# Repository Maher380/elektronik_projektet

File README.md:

# 🔥 CnB - Crash and Burn

Autonomous car school project built with C++ and ESP-IDF for the ESP32-S3.

This repository is used by team **CnB (Crash and Burn)** to develop the
software for an autonomous competition car.

The project starts from an ESP32-S3 driver library and includes:

- hardware abstraction through driver interfaces
- ESP32-S3 implementations for hardware-level code
- stubs for testing without hardware
- factory-based driver creation
- ESP-IDF CMake project structure

## Project Layout

```text
.
+-- 📁 firmware/                  ESP-IDF firmware project for the ESP32-S3
|   +-- CMakeLists.txt             Firmware project entry point
|   +-- 📁 main/                   Main ESP-IDF component
|       +-- CMakeLists.txt         Component source list and dependencies
|       +-- Kconfig.projbuild      Project configuration used by menuconfig
|       +-- 📁 include/            Public C++ headers
|       |   +-- 📁 driver/         Hardware driver interfaces and implementations
|       |   +-- 📁 system/         System-level interfaces and logic headers
|       +-- 📁 source/             C++ source files
|           +-- 📁 driver/         ADC, GPIO, timer, WiFi and serial drivers
|           +-- 📁 system/         Application logic and pin manager
|           +-- main.cpp           ESP-IDF application entry point
+-- 📁 hardware/                  Hardware design files
|   +-- 📁 kicad/                  KiCad schematics, PCB layout and exports
|   +-- 📁 ltspice/                LTspice simulations and component models
+-- README.md                      Project overview and workflow rules
+-- THIRD_PARTY_NOTICES.md         Attribution for imported starter code
```

The repository is split into two main areas:

- 📁 `firmware/` contains all software and embedded code.
- 📁 `hardware/` contains electronics design files, simulations and exports.

## Build

Use the ESP-IDF shell to build and flash:

```bash
cd firmware
idf.py set-target esp32s3
idf.py build
idf.py -p <PORT> flash monitor
```

Serial output is enabled over USB for later sensor testing. The application
prints `CnB serial ready` after the serial driver starts.

WiFi settings are configured with:

```bash
idf.py menuconfig
```

Open `Autonomous car network configuration` and set SSID and password. Do not
commit generated `sdkconfig` files with private credentials.

## Hardware

Hardware files are stored in `hardware/`.

- 📁 `hardware/kicad/` - KiCad project files for schematics, PCB layout, symbols, footprints and generated exports.
- 📁 `hardware/ltspice/` - LTspice simulation files, component models and circuit experiments.

## Branch Naming

Do not work directly on `main`. Create a branch for every task.

Branch names must use this format:

```text
<type>/<short-english-title>
```

Use a short English title. Prefer lowercase words separated with hyphens.

Allowed branch types:

- `feature/` - new functionality
- `fix/` - fixes for broken behavior
- `docs/` - documentation-only work
- `experiment/` - exploratory work not meant to be permanent
- `refactor/` - internal code cleanup without changing behavior
- `test/` - test-only changes
- `chore/` - maintenance, tooling or dependency updates
- `release/` - preparing a release
- `ci/` - pipeline or automation changes

Examples:

```bash
git switch -c docs/create-diary-structure
git switch -c feature/support-ir-sensor
```

If a branch belongs to a Jira task, include the Jira key in commits and pull
request titles:

```bash
git commit -m "CAR-12 support IR sensor"
```

## Pull Requests

Push your branch and open a pull request into `main`.

Each pull request should include:

- what was changed
- how it was tested
- the related Jira task, if one exists

## Vagrant system logic

The Vagrant logic runs the integrated IR/motor/servo loop. `main.cpp` starts
the target logic selected under Target car in `idf.py menuconfig`. Ford and the
third car are placeholders that leave the motor disabled until implemented.
See [system test setup and MQTT extensions](documentation/guides/main_system_test.md)
for wiring, behavior, configuration and host tests.

## Attribution

This project includes code derived from
`OliverEdman/cpp-driver-library-p02`, licensed under MIT. See
`THIRD_PARTY_NOTICES.md`.

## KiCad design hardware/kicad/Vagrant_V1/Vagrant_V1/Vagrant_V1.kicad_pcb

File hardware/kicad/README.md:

# KiCad

Place KiCad files here.

Typical files:

- `*.kicad_pro` - KiCad project
- `*.kicad_sch` - schematic
- `*.kicad_pcb` - PCB layout
- `symbols/` - project symbols
- `footprints/` - project footprints
- `exports/` - generated PDFs, Gerbers and BOM files

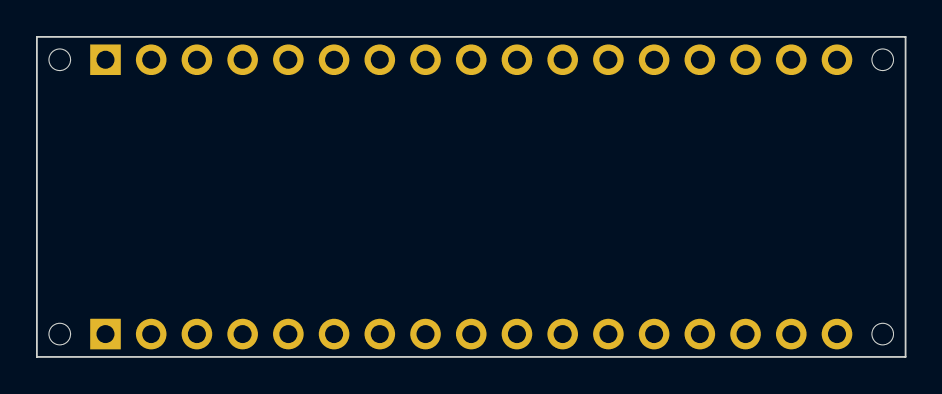
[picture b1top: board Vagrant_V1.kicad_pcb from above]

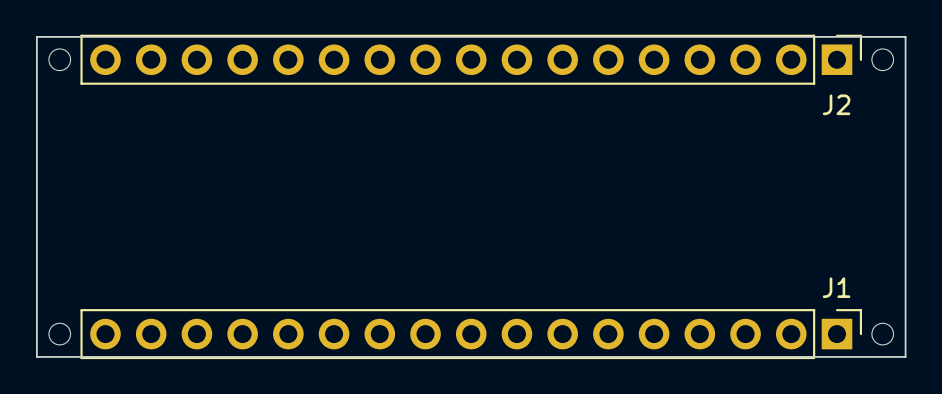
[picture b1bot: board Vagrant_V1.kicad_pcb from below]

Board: 2 copper layers, 48.3 x 17.8 mm, 6 parts (2 on the bottom side), 2 nets, no tracks yet.

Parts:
J1: Analog; PinHeader_1x17_P2.54mm_Vertical
J2: Digital; PinHeader_1x17_P2.54mm_Vertical
MH1, MH2, MH3, MH4: MountingHole_1.2mm

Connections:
/~RESET: J1.13, J2.13
GND: J1.14, J2.12
